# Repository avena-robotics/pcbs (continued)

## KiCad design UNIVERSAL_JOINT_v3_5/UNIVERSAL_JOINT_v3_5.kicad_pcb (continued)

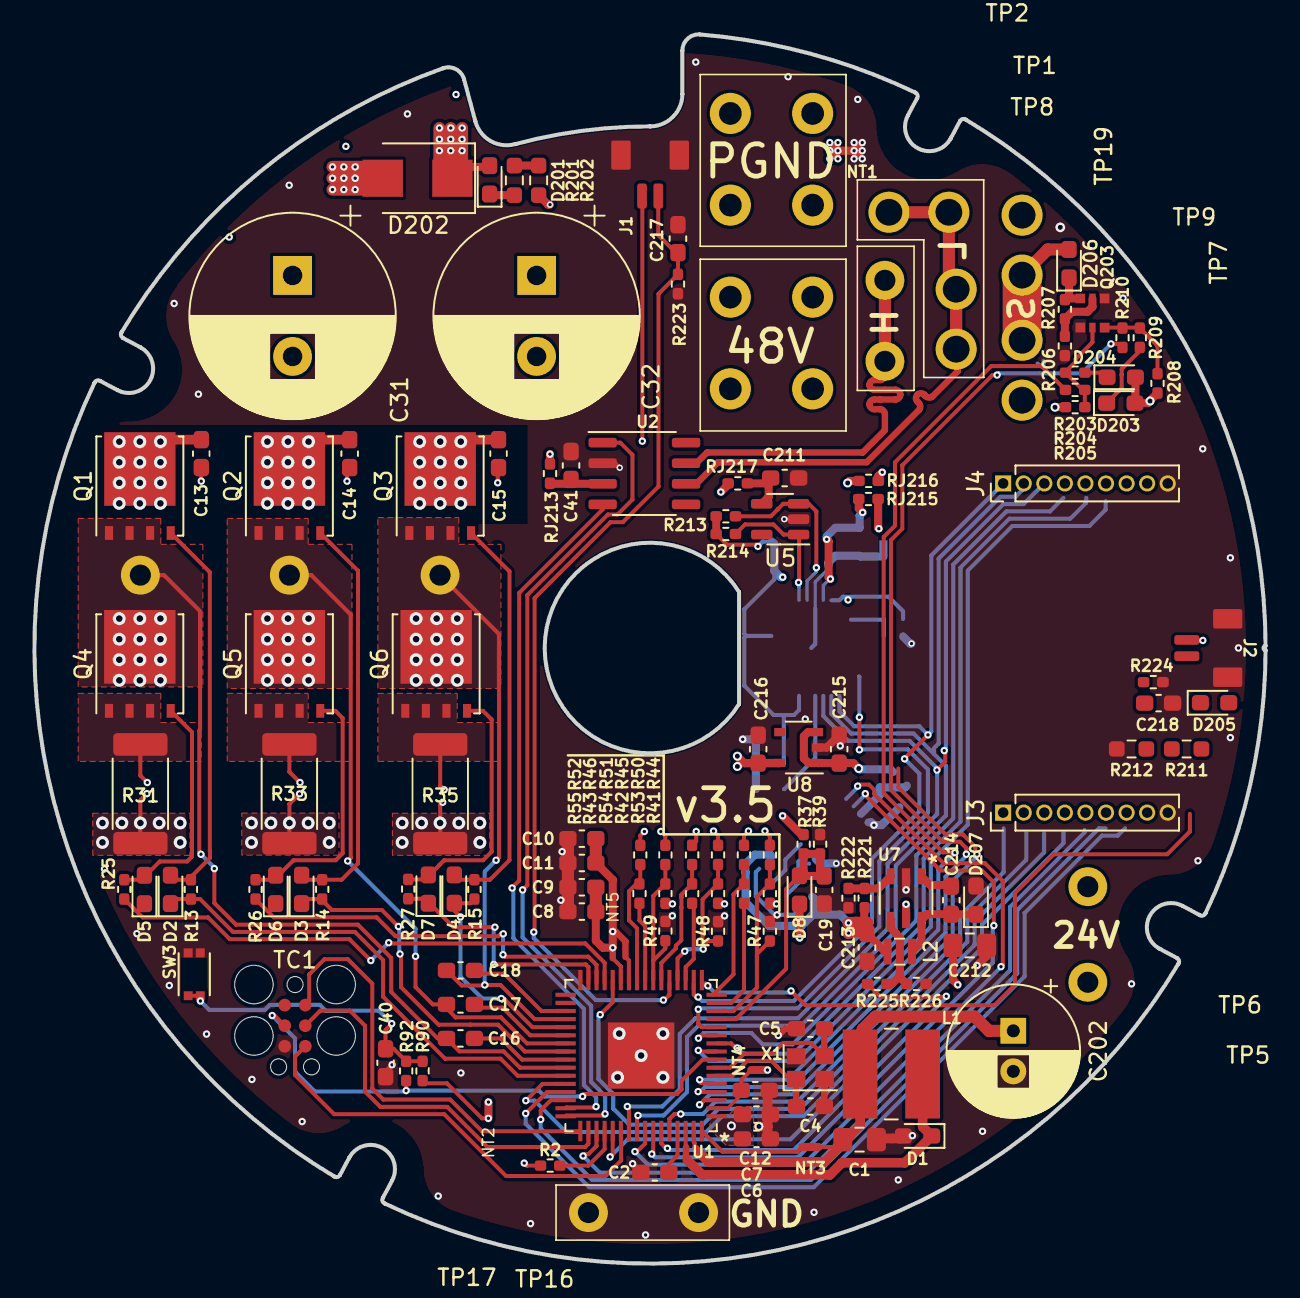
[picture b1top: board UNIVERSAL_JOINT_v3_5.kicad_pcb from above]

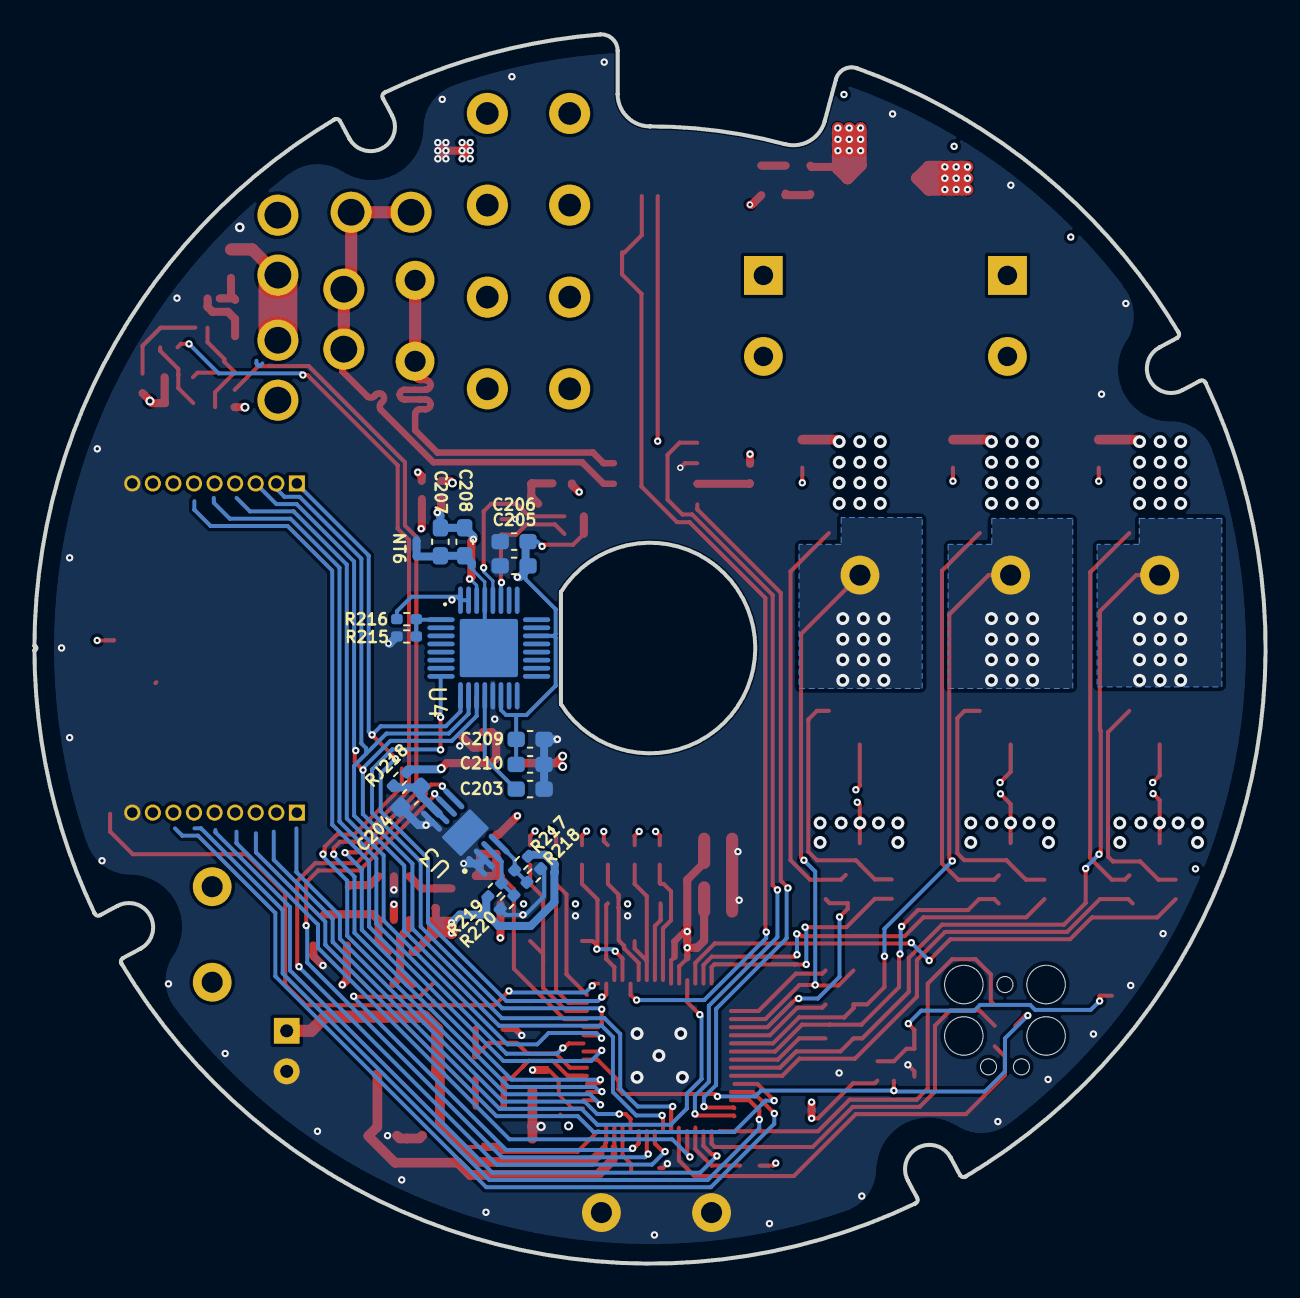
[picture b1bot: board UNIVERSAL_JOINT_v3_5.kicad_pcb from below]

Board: 4 copper layers, 76.0 x 75.9 mm, 160 parts (18 on the bottom side), 94 nets.

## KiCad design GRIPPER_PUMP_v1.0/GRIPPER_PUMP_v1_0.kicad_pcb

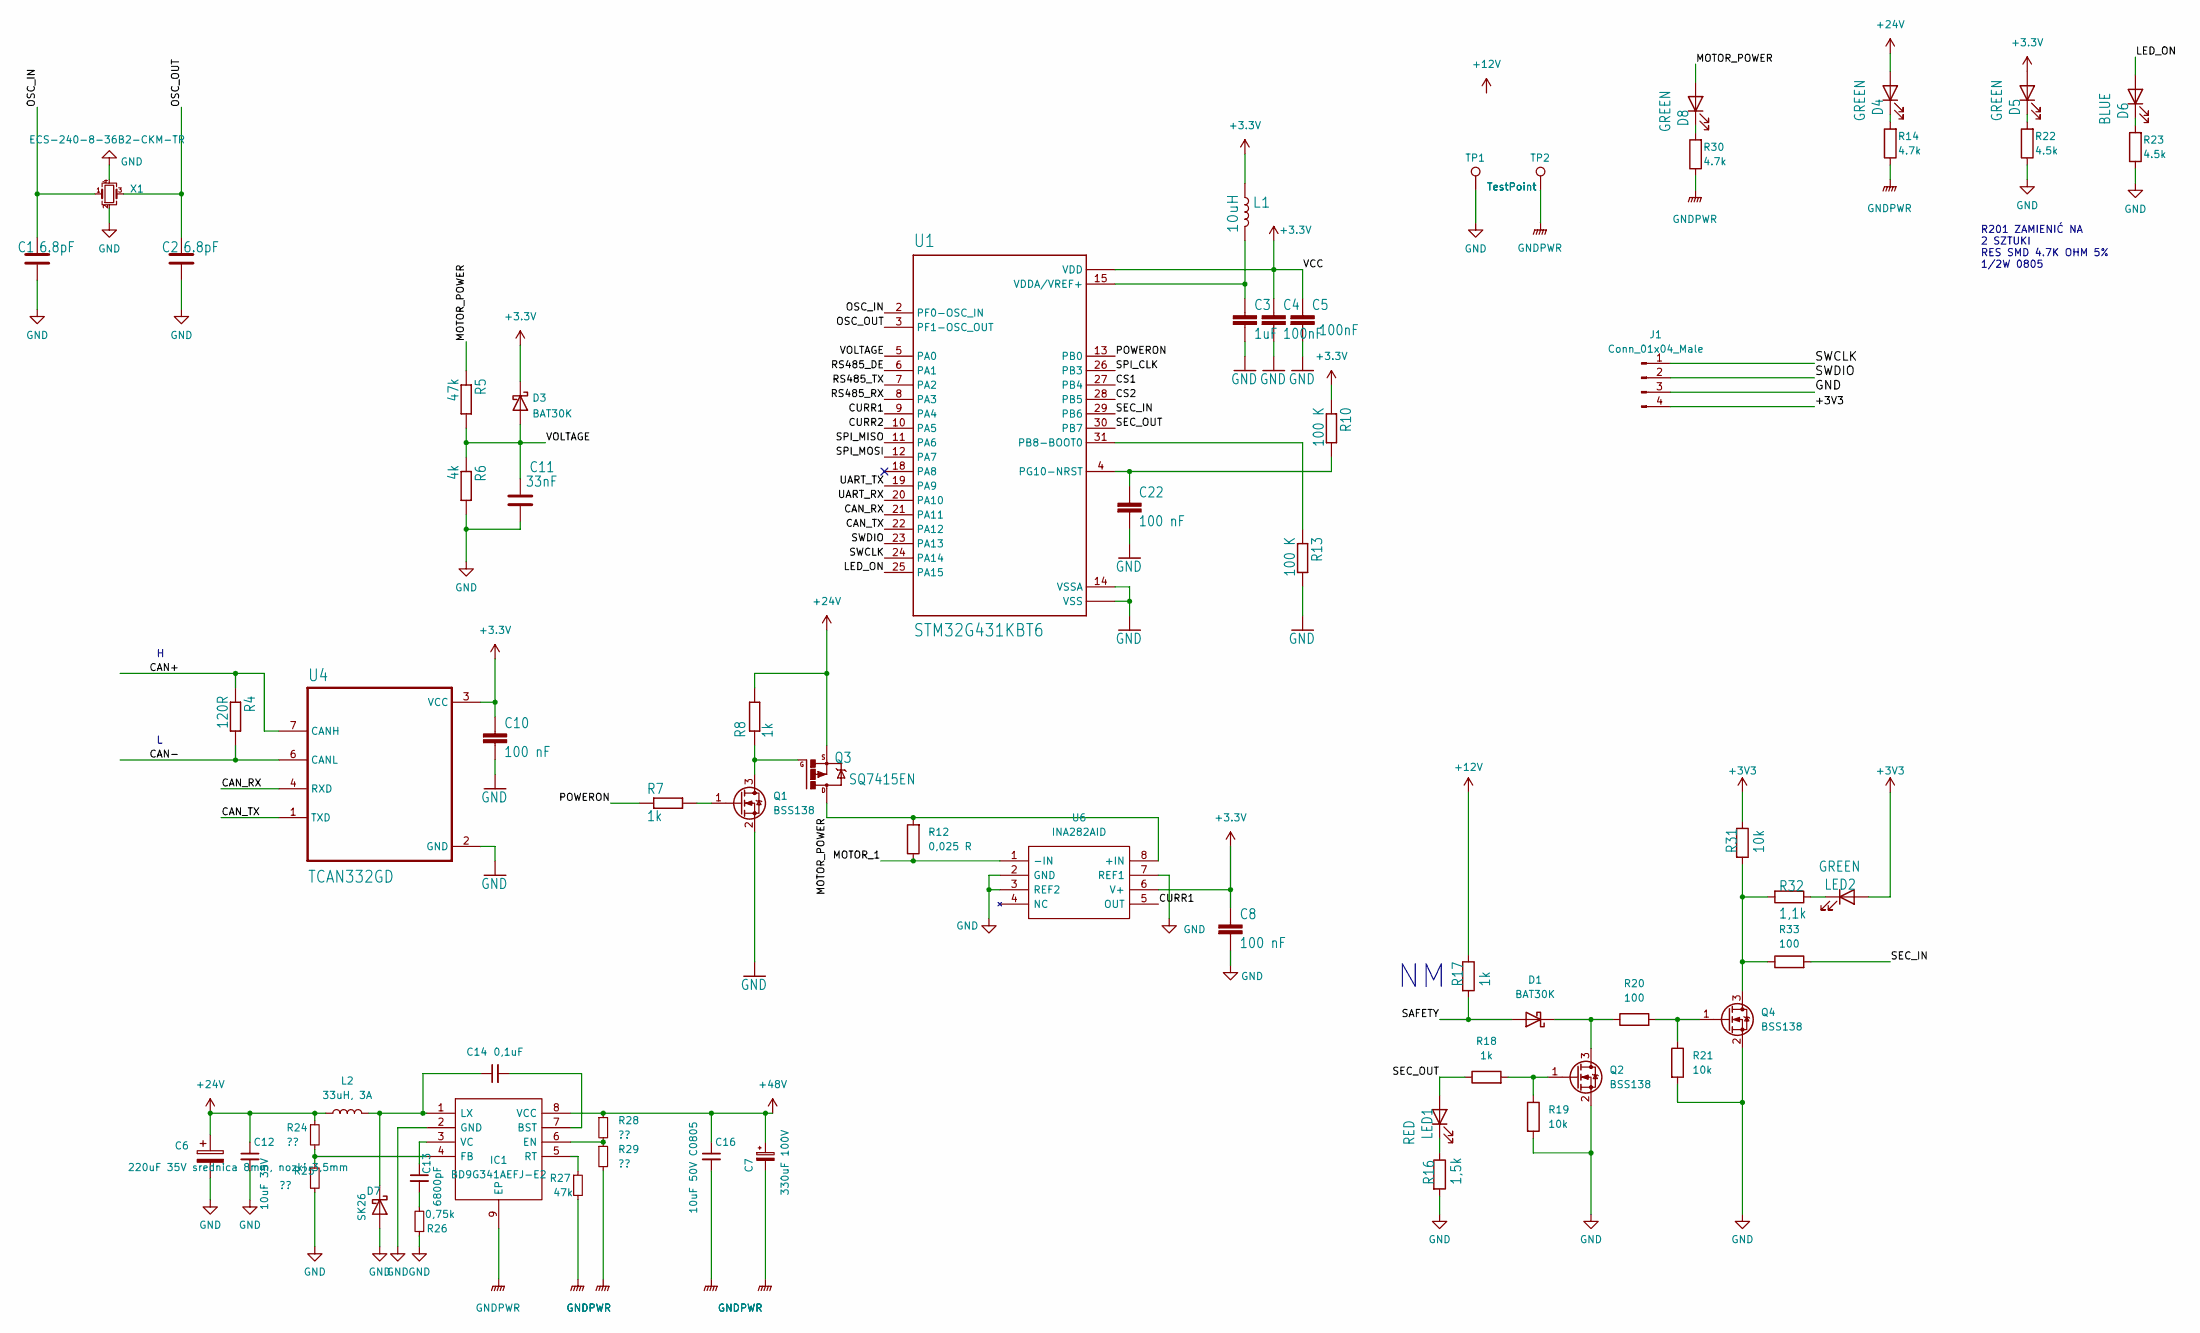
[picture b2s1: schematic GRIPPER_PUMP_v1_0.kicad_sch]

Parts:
C1, C2: 6.8pF; C_0603_1608Metric_Pad1.08x0.95mm_HandSolder
C3: 1uF; C_0603_1608Metric_Pad1.08x0.95mm_HandSolder
C4, C5: 100nF; C_0603_1608Metric_Pad1.08x0.95mm_HandSolder
C6: 220uF 35V srednica 8mm, nozki 3,5mm; C_Radial_D8.0mm_H11.5mm_P3.50mm
C7: 330uF 100V; CP_Radial_D12.5mm_P7.50mm
C8, C10, C22: 100 nF; C_0603_1608Metric_Pad1.08x0.95mm_HandSolder
C11: 33nF; C_0603_1608Metric_Pad1.08x0.95mm_HandSolder
C12: 10uF 35V; C_1206_3216Metric_Pad1.33x1.80mm_HandSolder
C13: 6800pF; C_0603_1608Metric_Pad1.08x0.95mm_HandSolder
C14: 0,1uF; C_0603_1608Metric_Pad1.08x0.95mm_HandSolder
C16: 10uF 50V C0805; C_0603_1608Metric_Pad1.08x0.95mm_HandSolder
D1, D3: BAT30K; D_0603_1608Metric_Pad1.05x0.95mm_HandSolder
D4, D5, D8: GREEN; D_0603_1608Metric_Pad1.05x0.95mm_HandSolder
D6: BLUE; D_0603_1608Metric_Pad1.05x0.95mm_HandSolder
D7: SK26; D_SMB_Handsoldering
IC1: BD9G341AEFJ-E2; SOIC127P600X100-9N; Mouser Part Number 755-BD9G341AEFJ-E2
J1: Conn_01x04_Male; PinHeader_1x04_P2.54mm_Vertical
L1: 10uH; 0603
L2: 33uH, 3A; MPEV1D1040L330
LED1: RED; D_0603_1608Metric_Pad1.05x0.95mm_HandSolder
LED2: GREEN; D_0603_1608Metric_Pad1.05x0.95mm_HandSolder
Q1, Q2, Q4: BSS138; SOT-23
Q3: SQ7415EN; DFN3.3X3.3
R4: 120R; R_0603_1608Metric_Pad0.98x0.95mm_HandSolder
R5, R27: 47k; R_0603_1608Metric_Pad0.98x0.95mm_HandSolder
R6: 4k; R_0603_1608Metric_Pad0.98x0.95mm_HandSolder
R7, R8, R17, R18: 1k; R_0603_1608Metric_Pad0.98x0.95mm_HandSolder
R10, R13: 100 K; R_0603_1608Metric_Pad0.98x0.95mm_HandSolder
R12: 0,025 R; R_2512_6332Metric_Pad1.40x3.35mm_HandSolder
R14, R30: 4.7k; R_0805_2012Metric_Pad1.20x1.40mm_HandSolder
R16: 1,5k; R_0603_1608Metric_Pad0.98x0.95mm_HandSolder
R19, R21, R31: 10k; R_0603_1608Metric_Pad0.98x0.95mm_HandSolder
R20, R33: 100; R_0603_1608Metric_Pad0.98x0.95mm_HandSolder
R22, R23: 4.5k; R_0603_1608Metric_Pad0.98x0.95mm_HandSolder
R24, R25, R28, R29: ??; R_0603_1608Metric_Pad0.98x0.95mm_HandSolder
R26: 0,75k; R_0603_1608Metric_Pad0.98x0.95mm_HandSolder
R32: 1,1k; R_0603_1608Metric_Pad0.98x0.95mm_HandSolder
TP1, TP2: TestPoint; TestPoint_Pad_1.0x1.0mm
U1: STM32G431KBT6; QFP80P900X900X160-32N
U4: TCAN332GD; SOIC127P599X175-8N
U6: INA282AID; SOIC127P600X175-8N; Mouser Part Number 595-INA282AID
X1: ECS-240-8-36B2-CKM-TR; Crystal_SMD_2520-4Pin_2.5x2.0mm

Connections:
+12V: R17.1
+24V: C6.1, C12.1, D4.2 (A), L2.1, Q3.1 (S), Q3.2 (S), Q3.3 (S), R8.2, R24.1
+48V: C7.1, C16.1, IC1.8 (VCC), R28.1
/CAN+: R4.1, U4.7 (CANH)
/CAN-: R4.2, U4.6 (CANL)
/CAN_RX: U1.21 (PA11), U4.4 (RXD)
/CAN_TX: U1.22 (PA12), U4.1 (TXD)
/CS1: U1.27 (PB4)
/CS2: U1.28 (PB5)
/CURR1: U1.9 (PA4), U6.5 (OUT)
/CURR2: U1.10 (PA5)
/LED_ON: D6.2 (A), U1.25 (PA15)
/MOTOR_1: R12.1, U6.1 (-IN)
/MOTOR_POWER: D8.2 (A), Q3.5 (D), Q3.6 (D), Q3.7 (D), Q3.8 (D), R5.1, R12.2, U6.8 (+IN)
/OSC_IN: C1.2, U1.2 (PF0-OSC_IN), X1.1
/OSC_OUT: C2.2, U1.3 (PF1-OSC_OUT), X1.3
/POWERON: R7.1, U1.13 (PB0)
/RS485_DE: U1.6 (PA1)
/RS485_RX: U1.8 (PA3)
/RS485_TX: U1.7 (PA2)
/SAFETY: D1.2 (A), R17.2
/SEC_IN: R33.2, U1.29 (PB6)
/SEC_OUT: LED1.2 (A), R18.1, U1.30 (PB7)
/SPI_CLK: U1.26 (PB3)
/SPI_MISO: U1.11 (PA6)
/SPI_MOSI: U1.12 (PA7)
/SWCLK: J1.1, U1.24 (PA14)
/SWDIO: J1.2, U1.23 (PA13)
/UART_RX: U1.20 (PA10)
/UART_TX: U1.19 (PA9)
/VOLTAGE: C11.2, D3.2 (A), R5.2, R6.1, U1.5 (PA0)
GND: C1.1, C2.1, C3.2, C4.2, C5.2, C6.2, C8.2, C10.2, C11.1, C12.2, C22.2, D7.2 (A), IC1.2 (GND), J1.3, Q1.2 (S), Q2.2 (S), Q4.2 (S), R6.2, R13.2, R16.2, R19.2, R21.2, R22.1, R23.1, R25.2, R26.1, TP1.1, U1.14 (VSSA), U1.16 (VSS), U1.32 (VSS), U4.2 (GND), U6.2 (GND), U6.3 (REF2), U6.7 (REF1), X1.2, X1.4
GNDPWR: C7.2, C16.2, IC1.9 (EP), R14.1, R27.2, R29.2, R30.1, TP2.1
unnamed: C3.1, L1.2, U1.15 (VDDA/VREF+)
unnamed: C13.1, IC1.3 (VC)
unnamed: C13.2, R26.2
unnamed: C14.1, D7.1 (K), IC1.1 (LX), L2.2
unnamed: C14.2, IC1.7 (BST)
unnamed: C22.1, R10.2, U1.4 (PG10-NRST)
unnamed: D1.1 (K), Q2.3 (D), R20.1
unnamed: D4.1 (K), R14.2
unnamed: D5.1 (K), R22.2
unnamed: D6.1 (K), R23.2
unnamed: D8.1 (K), R30.2
unnamed: IC1.4 (FB), R24.2, R25.1
unnamed: IC1.5 (RT), R27.1
unnamed: IC1.6 (EN), R28.2, R29.1
unnamed: LED1.1 (K), R16.1
unnamed: LED2.1 (K), R32.1
unnamed: Q2.1 (G), R18.2, R19.1
unnamed: Q1.3 (D), Q3.4 (G), R8.1
unnamed: Q4.1 (G), R20.2, R21.1
unnamed: Q4.3 (D), R31.2, R32.2, R33.1
unnamed: Q1.1 (G), R7.2
unnamed: R13.1, U1.31 (PB8-BOOT0)

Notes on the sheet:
R201 ZAMIENIĆ NA 2 SZTUKI RES SMD 4.7K OHM 5% 1/2W 0805

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
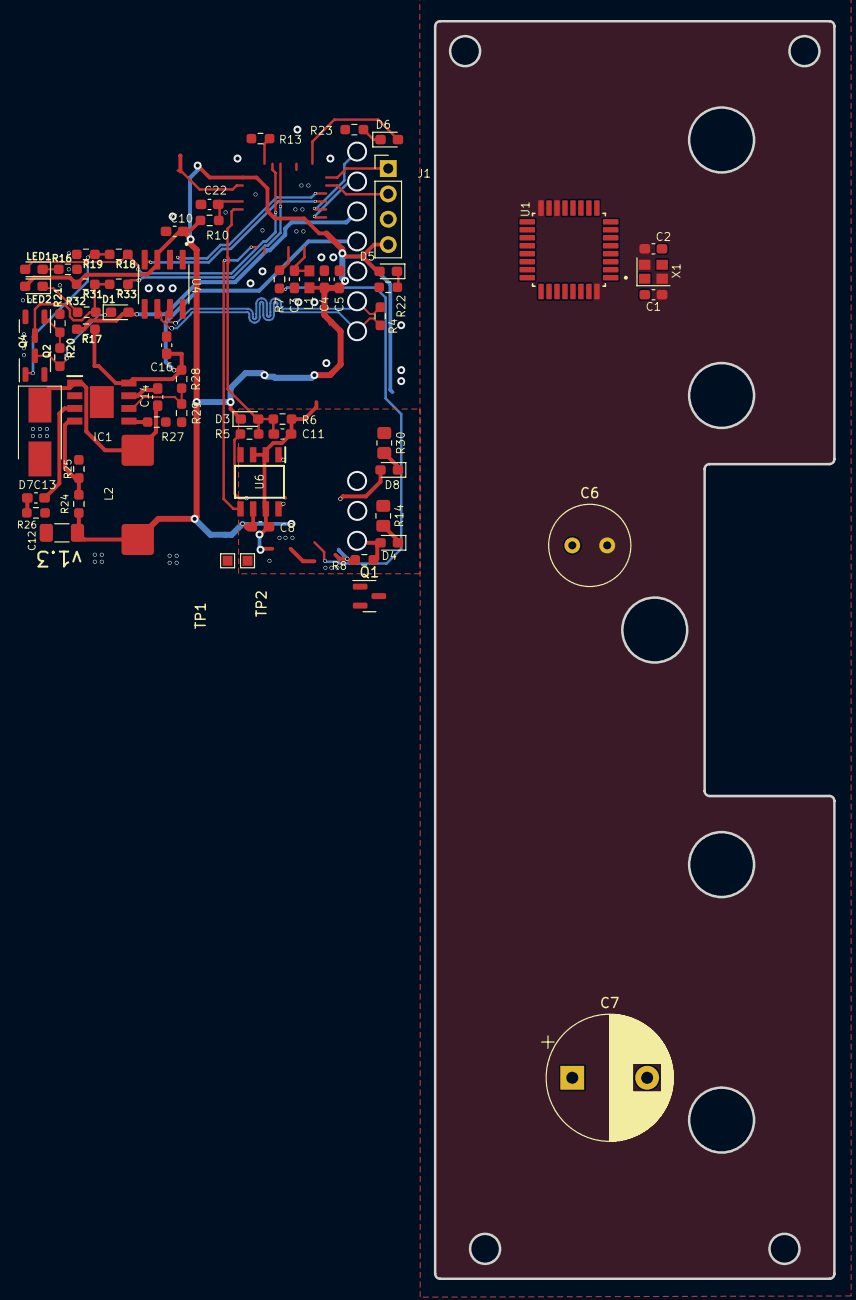
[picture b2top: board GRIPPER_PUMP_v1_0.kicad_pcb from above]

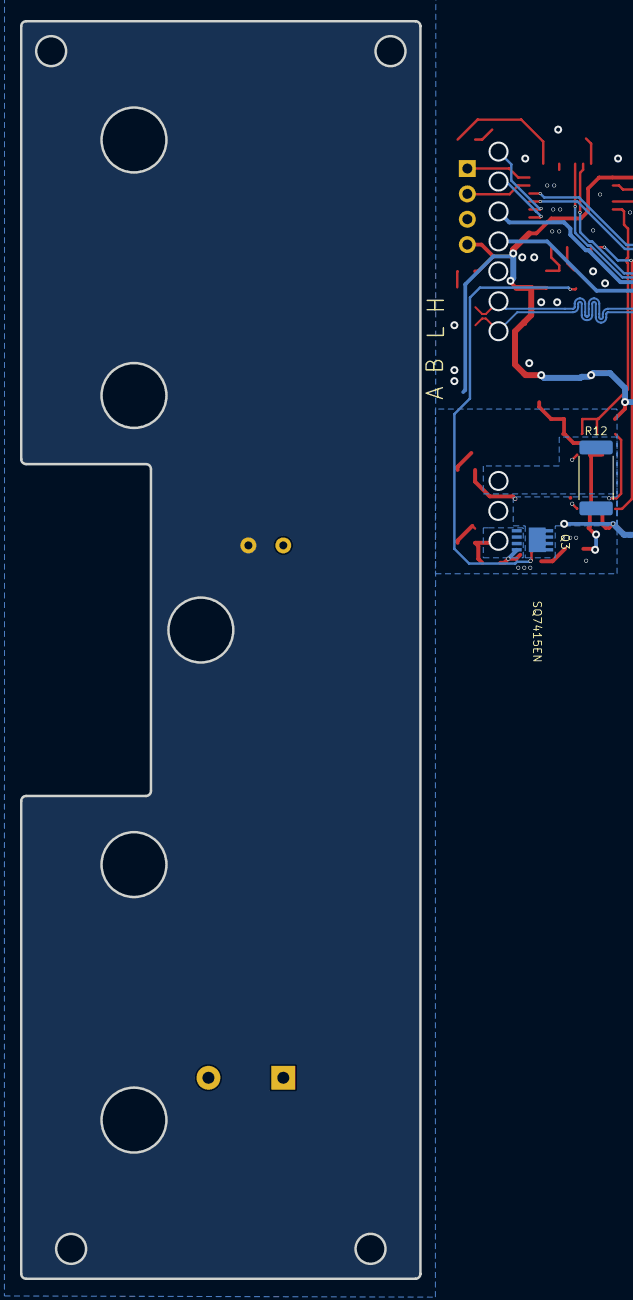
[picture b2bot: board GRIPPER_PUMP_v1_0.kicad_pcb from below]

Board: 2 copper layers, 40.0 x 126.0 mm, 65 parts (2 on the bottom side), 44 nets.

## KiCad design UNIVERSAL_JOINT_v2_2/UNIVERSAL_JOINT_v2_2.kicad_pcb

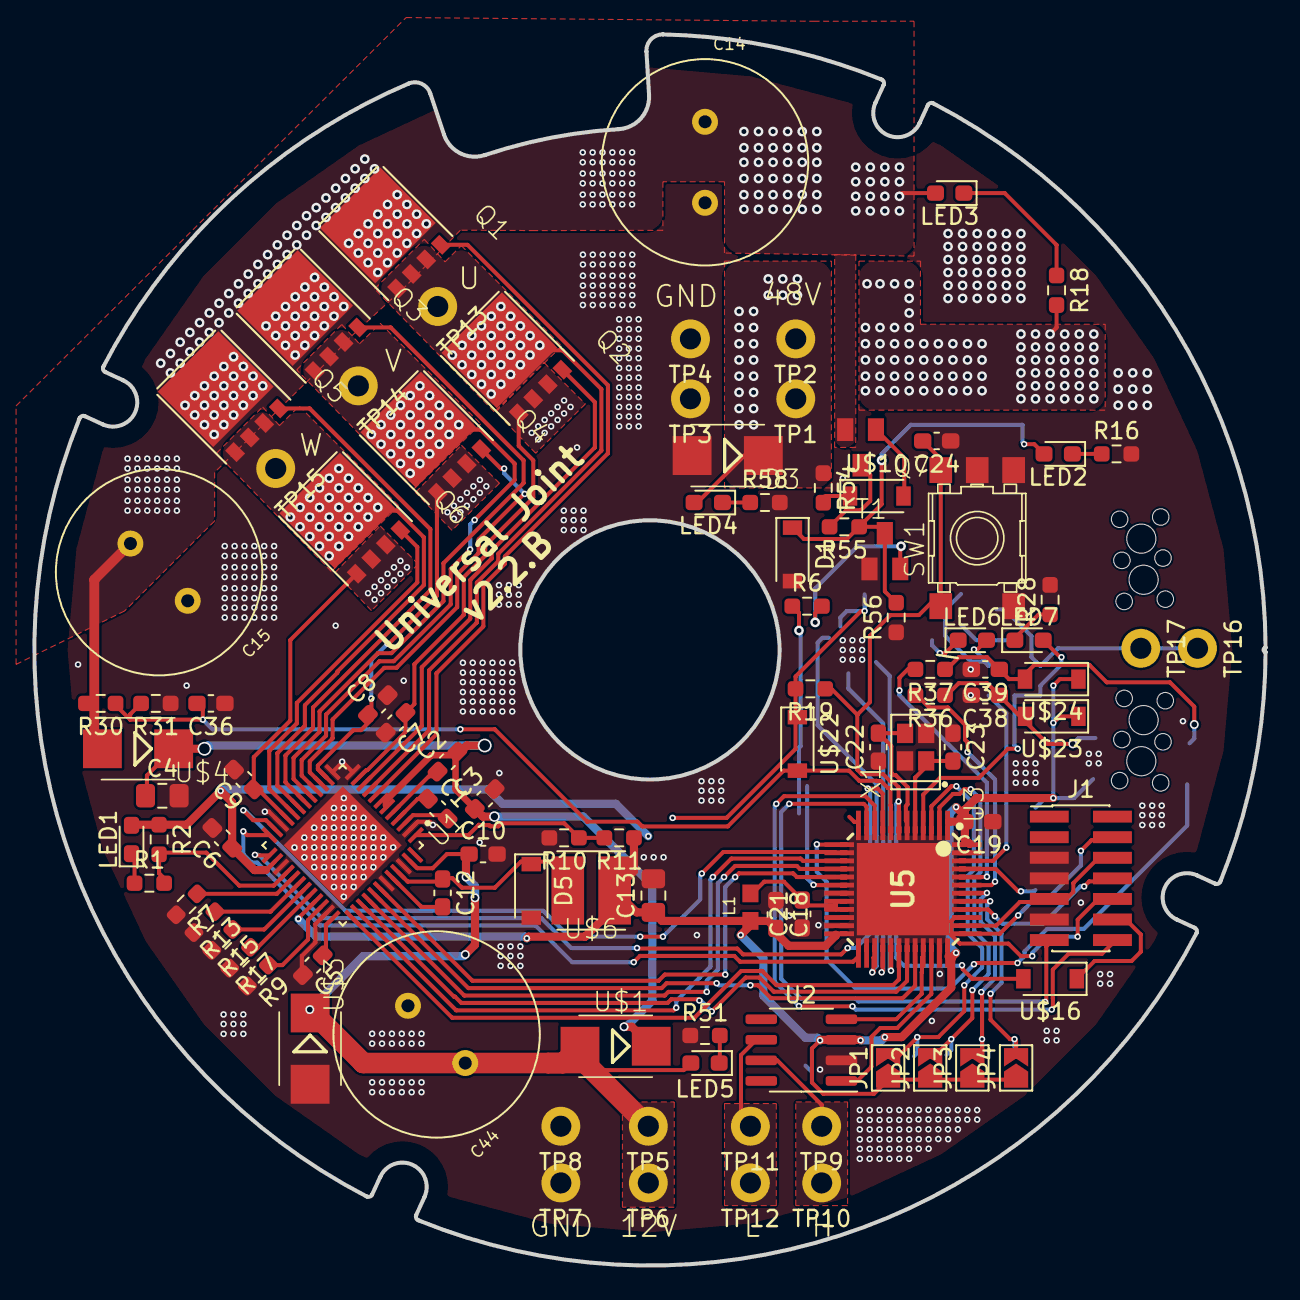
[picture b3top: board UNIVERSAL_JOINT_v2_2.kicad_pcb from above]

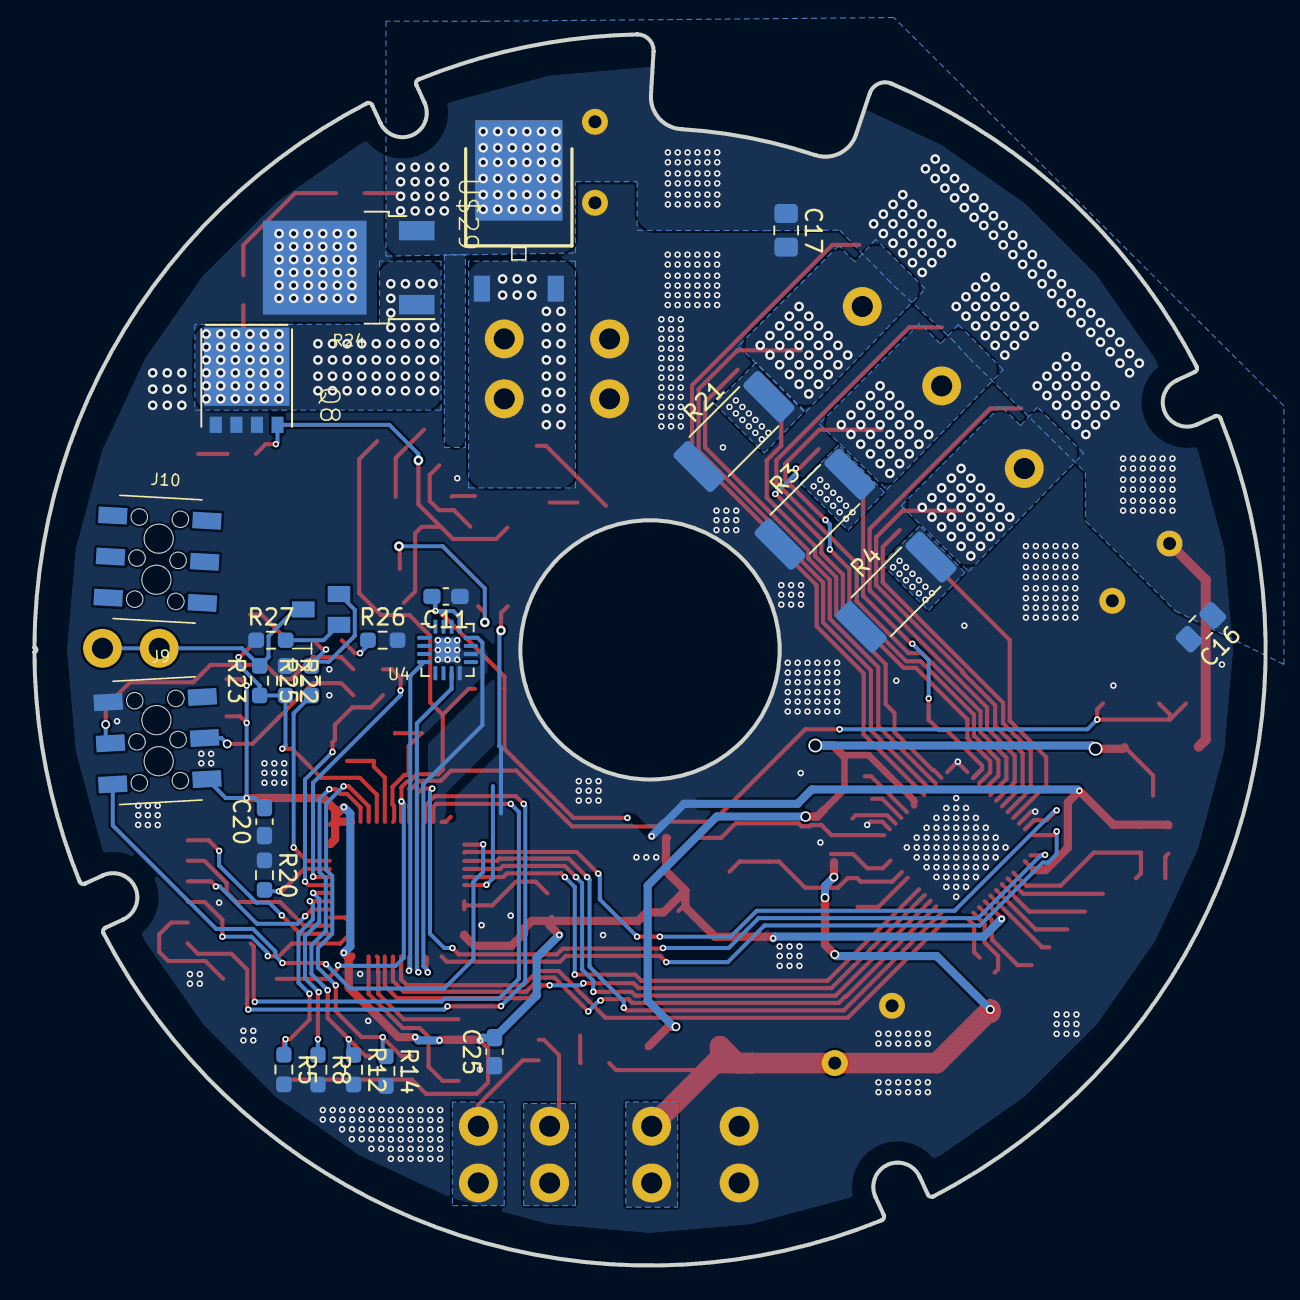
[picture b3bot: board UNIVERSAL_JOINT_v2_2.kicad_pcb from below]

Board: 2 copper layers, 76.0 x 76.0 mm, 128 parts (25 on the bottom side), 89 nets.

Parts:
C1: 47nF x 50V; C_0603_1608Metric_Pad1.08x0.95mm_HandSolder
C2, C10, C11, C21: 1uF; C_0603_1608Metric_Pad1.08x0.95mm_HandSolder
C3, C5, C6, C12, C18, C19, C20, C24, C25: 100nF; C_0603_1608Metric_Pad1.08x0.95mm_HandSolder
C4: 10uF; C_0805_2012Metric_Pad1.18x1.45mm_HandSolder
C7, C8, C9: 1nF; C_0603_1608Metric_Pad1.08x0.95mm_HandSolder
C13: 22u; C_0805_2012Metric_Pad1.18x1.45mm_HandSolder
C14, C15, C44: 330uF; C_Radial_D12.5mm_H25.0mm_P5.00mm
C16, C17: 100nF; C_0805_2012Metric_Pad1.18x1.45mm_HandSolder
C22, C23: 22pF; C_0603_1608Metric_Pad1.08x0.95mm_HandSolder
C36: 4.7n x 10V; C_0603_1608Metric_Pad1.08x0.95mm_HandSolder
C38, C39: 4.7nF; C_0603_1608Metric_Pad1.08x0.95mm_HandSolder
D1: ACZRW5242B-G; D_SOD-123
D3: SMBJ48A-TR; SMB
D5: MBR1H100SFT3G; D_SOD-123
J1: Conn_02x07_Odd_Even; PinHeader_2x07_P1.27mm_Vertical_SMD
J9: HEADER_MALE_2X3_2.54_SMT; M207810345
J10: n.m.; M207810345
JP1, JP2, JP3, JP4: SolderJumper_2_Open; SolderJumper-2_P1.3mm_Open_TrianglePad1.0x1.5mm
L1: 10uH; 0603
LED1, LED6: RED; D_0603_1608Metric_Pad1.05x0.95mm_HandSolder
LED2: BLUE; D_0603_1608Metric_Pad1.05x0.95mm_HandSolder
LED3: ORANGE; D_0603_1608Metric_Pad1.05x0.95mm_HandSolder
LED4, LED5, LED7: GREEN; D_0603_1608Metric_Pad1.05x0.95mm_HandSolder
Q1, Q2, Q3, Q4, Q5, Q6, Q8: IAUC120N06S5L; SO-8FL
Q7: ZXTP19100CFFCT; SOT23
R1, R26: 130R; R_0603_1608Metric_Pad0.98x0.95mm_HandSolder
R2, R6, R51: 1k; R_0603_1608Metric_Pad0.98x0.95mm_HandSolder
R3, R4, R21: 10mR; R_2512_6332Metric_Pad1.40x3.35mm_HandSolder
R5, R8, R12, R14, R19, R20: 100k; R_0603_1608Metric_Pad0.98x0.95mm_HandSolder
R7, R17: 0; R_0603_1608Metric_Pad0.98x0.95mm_HandSolder
R9, R10, R54, R56: 10k; R_0603_1608Metric_Pad0.98x0.95mm_HandSolder
R11: 33k; R_0603_1608Metric_Pad0.98x0.95mm_HandSolder
R13, R15: 75k; R_0603_1608Metric_Pad0.98x0.95mm_HandSolder
R16: 1.2k; R_0603_1608Metric_Pad0.98x0.95mm_HandSolder
R18: 4.6k; R_0603_1608Metric_Pad0.98x0.95mm_HandSolder
R22: 5,23k; R_0603_1608Metric_Pad0.98x0.95mm_HandSolder
R23: 13,7k; R_0603_1608Metric_Pad0.98x0.95mm_HandSolder
R24: 47R; TO-252-2
R25, R27: 200R; R_0603_1608Metric_Pad0.98x0.95mm_HandSolder
R28: 80R; R_0603_1608Metric_Pad0.98x0.95mm_HandSolder
R30: 169k; R_0603_1608Metric_Pad0.98x0.95mm_HandSolder
R31: 9k31; R_0603_1608Metric_Pad0.98x0.95mm_HandSolder
R36, R37: 1k8; R_0603_1608Metric_Pad0.98x0.95mm_HandSolder
R55: 22k; R_0603_1608Metric_Pad0.98x0.95mm_HandSolder
R58: 4.5k; R_0603_1608Metric_Pad0.98x0.95mm_HandSolder
SW1: SKHMPE010; SKHMPXE010
T1, T2: 2PC4081S,115; SOT23-EBC
TP1, TP2, TP3, TP4, TP5, TP6, TP7, TP8, TP9, TP10, TP11, TP12, TP13, TP14, TP15, TP16, TP17: TestPoint; 61-2348-11_0030
U1: DRV8323RHRGZR; QFN50P700X700X100-49N
U2: TCAN332G; SOIC-8_3.9x4.9mm_P1.27mm
U3: STM32G431C8T6; LQFP48-7X7
U4: MA730; HVQFN-16-1EP_3x3mm_P0.5mm_EP1.5x1.5mm
U5: STM32G431CBU6; QFN50P700X700X65-49N-D
U$1, U$4: SMBJ48A-TR; SMB
U$3: 16V; SMB
U$6: SRN4012TA-150M; BEADC4040X120N
U$10: STPS0560Z; D_SOD-123
U$16, U$22, U$23, U$24: RSX101M-30TR; D_SOD-123
U$29: MBRD10100CT; DPACK
X1: LFXTAL069392CUTT; 2.5X2-4-PAD

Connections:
+3V3: C6.1, C11.2, C13.1, C18.2, C19.2, C20.2, C25.2, J9.6, JP1.1 (A), JP2.1 (A), JP3.1 (A), JP4.1 (A), L1.1, LED1.2 (A), R2.1, R11.1, R19.2, U1.26 (VREF), U1.33 (ENABLE), U2.3 (VCC), U3.1 (VDD), U3.24 (VDD), U3.36 (VDD), U3.48 (VDD), U4.13 (VDD), U$6.1, U$22.1 (K), U$23.1 (K), U$24.1 (K)
/12V: C10.1, C44.1, LED5.2 (A), TP5.1, TP6.1, U1.47 (VIN), U$1.A, U$3.C
/48V: D3.C, LED4.2 (A), R54.1, TP1.1, TP2.1, U$29.1 (A1), U$29.3 (A2)
/A: C38.1, J9.4, R36.1, U$23.2 (A)
/B: C39.1, J9.3, R37.1, U$24.2 (A)
/BRAKE: R6.1, U3.12 (PA4), U5.12 (PA4)
/CAN_H: TP9.1, TP10.1, U2.7 (CANH)
/CAN_L: TP11.1, TP12.1, U2.6 (CANL)
/CB: C12.2, U1.44 (CB)
/CS1: U3.18 (PB2), U4.5 (~CS)
/CURR_FB_U: U1.25 (SOA), U3.9 (PA1), U5.9 (PA1)
/CURR_FB_V: U1.24 (SOB), U3.25 (PB11)
/CURR_FB_W: U1.23 (SOC), U3.14 (PA6), U5.14 (PA6)
/DIP1: JP1.2 (B), R14.1, U3.3 (PC14)
/DIP2: JP2.2 (B), R12.1, U3.2 (PC13)
/DIP3: JP3.2 (B), R8.1, U3.42 (PB5)
/DIP4: JP4.2 (B), R5.1, U3.41 (PB4)
/FDCAN_RX: U2.4 (RXD), U3.33 (PA11)
/FDCAN_TX: U2.1 (TXD), U3.34 (PA12)
/GAIN: R17.1, U1.32 (GA]N)
/GHA: Q1.P$4 (G), U1.8 (GHA)
/GHB: Q3.P$4 (G), U1.17 (GHB)
/GHC: Q5.P$4 (G), U1.18 (GHC)
/GLA: Q2.P$4 (G), U1.10 (GLA)
/GLB: Q4.P$4 (G), U1.15 (GLB)
/GLC: Q6.P$4 (G), U1.20 (GLC)
/H1: R36.2, U3.43 (PB6)
/H2: R37.2, U3.44 (PB7)
/IDRIVE: R13.1, U1.30 (IDRLVE)
/JTDI: J1.10, U3.39 (PA15)
/MODE: R7.1, U1.29 (MODE)
/MOTOR_SUPPLY: C14.1, C15.1, C16.1, C17.1, LED3.2 (A), Q1.P$5 (D), Q3.P$5 (D), Q5.P$5 (D), Q7.2 (E), R24.3, R30.2, U$4.A, U$29.2 (C)
/MOTOR_U: Q1.P$1 (S), Q1.P$2 (S), Q1.P$3 (S), Q2.P$5 (D), TP13.1, U1.9 (SHA)
/MOTOR_V: Q3.P$1 (S), Q3.P$2 (S), Q3.P$3 (S), Q4.P$5 (D), TP14.1, U1.16 (SHB)
/MOTOR_W: Q5.P$1 (S), Q5.P$2 (S), Q5.P$3 (S), Q6.P$5 (D), TP15.1, U1.19 (SHC)
/NFAULT: R1.2, R2.2, U1.28 (NFAULT)
/PWM_1: U1.37 (INHA), U3.30 (PA8)
/PWM_1N: U1.38 (INLA), U3.15 (PA7), U5.15 (PA7)
/PWM_2: U1.39 (INHB), U3.31 (PA9)
/PWM_2N: U1.40 (INLB), U3.16 (PB0), U5.17 (PB0)
/PWM_3: U1.41 (INHC), U3.32 (PA10)
/PWM_3N: U1.42 (INLC), U3.17 (PB1), U5.18 (PB1)
/SECURITY: R23.2, T2.C, TP16.1, TP17.1
/SEC_IN: LED7.2 (A), R22.2, R23.1, U3.4 (PC15)
/SEC_OUT: R25.1, U3.46 (PB9)
/SENS_U: C7.1, Q2.P$1 (S), Q2.P$2 (S), Q2.P$3 (S), R21.2, U1.11 (SPA)
/SENS_V: C8.1, Q4.P$1 (S), Q4.P$2 (S), Q4.P$3 (S), R3.2, U1.14 (SPB)
/SENS_W: C9.1, Q6.P$1 (S), Q6.P$2 (S), Q6.P$3 (S), R4.2, U1.21 (SPC)
/SPI_MISO: U3.28 (PB14), U4.7 (MISO)
/SPI_MOSI: U3.29 (PB15), U4.4 (MOSI)
/SPI_SCK: U3.27 (PB13), U4.12 (SCLK)
/SW: C12.1, D5.1 (K), U1.45 (SW), U$6.2
/SWCLK/JTCK: J1.6, J1.9, U3.38 (PA14)
/SWDIO/JTMS: J1.4, U3.37 (PA13)
/SWO/JTDO: J1.8, U3.40 (PB3)
/TEMP: J9.5, U3.13 (PA5), U5.13 (PA5)
/UART_RX: J1.13, U3.11 (PA3), U5.11 (PA3)
/UART_TX: J1.14, U3.10 (PA2), U5.10 (PA2)
/VBUS: C36.2, R30.1, R31.2, U3.8 (PA0), U5.8 (PA0), U$22.2 (A)
/VDS: R15.1, U1.31 (VDS)
/VM: C2.2, C3.1, C4.1, U1.6 (VM), U1.7 (VDRALN), U$1.C, U$4.C
/nRST: J1.12, U$16.1 (K)
GND: C3.2, C4.2, C5.2, C6.2, C7.2, C8.2, C9.2, C10.2, C11.1, C13.2, C14.2, C15.2, C16.2, C17.2, C18.1, C19.1, C20.1, C21.1, C22.1, C23.1, C24.1, C25.1, C36.1, C38.2, C39.2, C44.2, D1.2 (A), D3.A, D5.2 (A), J1.5, J1.7, J1.11, J9.1, Q8.P$1 (S), Q8.P$2 (S), Q8.P$3 (S), R3.1, R4.1, R5.2, R7.2, R8.2, R9.2, R10.2, R12.2, R13.2, R14.2, R15.2, R16.2, R17.2, R20.1, R21.1, R22.1, R24.2, R26.2, R27.1, R28.2, R31.1, R51.2, R56.1, R58.2, SW1.3 (2.1), SW1.4 (2.2), SW1.5 (SH), T1.E, TP3.1, TP4.1, TP7.1, TP8.1, U1.2 (PGND), U1.12 (SNA), U1.13 (SNB), U1.22 (SNC), U1.27 (DGND), U1.35 (AGND), U1.43 (BGND), U1.46 (NC), U1.49 (PAD), U2.2 (GND), U3.19 (VSSA), U3.23 (VSS), U3.35 (VSS), U3.47 (VSS), U4.8 (GND), U4.10 (TEST), U4.17 (PAD), U$3.A, X1.2, X1.4
unnamed: C1.1, U1.4 (CPH)
unnamed: C1.2, U1.3 (CPL)
unnamed: C2.1, U1.5 (VCP)
unnamed: C5.1, U1.36 (DVDD)
unnamed: C21.2, L1.2, U3.20 (VDDA/VREF+), U3.21 (VDDA/VREF+)
unnamed: C22.2, U3.6 (PF1-OSC_OUT), X1.3
unnamed: C23.2, U3.5 (PF0-OSC_IN), X1.1
unnamed: C24.2, R19.1, SW1.1 (1.1), SW1.2 (1.2), U3.7 (PG10-NRST), U$16.2 (A)
unnamed: D1.1 (K), LED2.2 (A), Q8.P$4 (G), R55.1, R56.2, T1.C
unnamed: LED1.1 (K), R1.1
unnamed: LED2.1 (K), R16.1
unnamed: LED3.1 (K), R18.1
unnamed: LED4.1 (K), R58.1
unnamed: LED5.1 (K), R51.1
unnamed: LED6.1 (K), R26.1
unnamed: LED6.2 (A), R25.2, T2.B
unnamed: LED7.1 (K), R28.1
unnamed: Q7.1 (B), U$10.2 (A)
unnamed: Q7.3 (C), R55.2
unnamed: Q8.P$5 (D), R18.2, R24.1
unnamed: R6.2, T1.B
unnamed: R9.1, U1.34 (CAL)
unnamed: R10.1, R11.2, U1.1 (FB)
unnamed: R20.2, U3.45 (PB8-BOOT0)
unnamed: R27.2, T2.E
unnamed: R54.2, U$10.1 (K)
